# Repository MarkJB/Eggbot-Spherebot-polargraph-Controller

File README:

CCNC 2015 Copyright Mark Benson etc etc

This is my Arduino Nano/Stepstick Eggbot/Shperebot/Polargraph control board.

This has been used sucessfully with a 3d printed Eggbot and Polargraph. Firmwares adapted for this board available in github.com/markjb.

Designed in Kicad and custom kicad libs included.

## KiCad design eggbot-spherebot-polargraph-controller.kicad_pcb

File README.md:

CC BY-NC-SA 2016 Copyright Mark Benson etc etc

__Note: The v2.1 board is missing a power track between U2 & U3. You will need to solder a jumper wire between the Vin pins or Stepper1 (U2) will not move!__ (This has been fixed with v2.2)

This is my Arduino Nano - Dual Stepstick drawing machine controller PCB for Eggbot/Shperebot/polargraph drawing machines. The reason this uses an Arduino Nano and external stepstick drivers is that they can be found on ebay for not much money and I wanted this to be an affordable way to build the electronics for various drawing machines.

This has been used sucessfully with a 3d printed Eggbot and polargraph. Firmwares adapted for this board available in github.com/markjb. I've also seen it working with the Gocupi firmware.

Micro-stepping is software controlled and both steppers share the same 3 Arduino pins, so you only need configure those 3 pins to set the micro stepping for both steppers.

Assembly should be straight forward.

Orientation of U1, U2 & U3 can be determined by matching the pin names.

Orientation of C1 & C2 is negative to white half of silkscreen.

P1 & P2 (Stepper motors) are wired (from pin 1) A1, A2, B1, B2

P3 & P4 (End stops) are wired for 'Makerbot' style end stops and are wired (from pin 1) Vcc, Gnd, Gnd, Signal

P5 (Servo) is wired (from pin 1) Signal, Vcc, Gnd

BoM

| QTY | Description |
| --- | ---|
| 1 | PCB |
| 1 | Arduino Nano (U1) |
| 2 | Stepstick stepper motor driver boards (DRV8825 or A4988) (U2,U3) |
| 2 | 100uF 35v Electrolitic Capacitor (C1, C2) |
| 4 | 8 way female header (U2,U3) |
| 2 | 15 way female header (these are hard to come by, but 16 way headers are much easier to find and will work if you cut off one of the end pins) (U1) |
| 1 | 6 way female header (P7) |
| 4 | 4 way male header (P1,P2,P3,P4) |
| 1 | 3 way male header (P5) |
| 1 | 2 way male header (P6) |
| 1 | 2 way jumper (P6) |
| 1 | DC socket (CON1) |

EXT PWR = External Power. Enables or disables powering the Arduino from the DC supply. I've had a few Arduino Nano clones go up in smoke when used with both external and USB power. Leave the jumper off EXT PWR unless you have a really good reason for wanting to power the Arduino from the DC supply. I had hoped to be able to enable the SPI SD card and load the command queue onto that and run long Polargrapgh drawings from that on DC power alone, but there are issues with firmware size.

End stops are optional. Might be useful on an Eggbot/Spherebot.

Designed in Kicad 4.0.x. Custom kicad libs included.

PCBs manufactured by iTead Studios PCB prototyping service https://www.itead.cc/open-pcb/pcb-prototyping.html

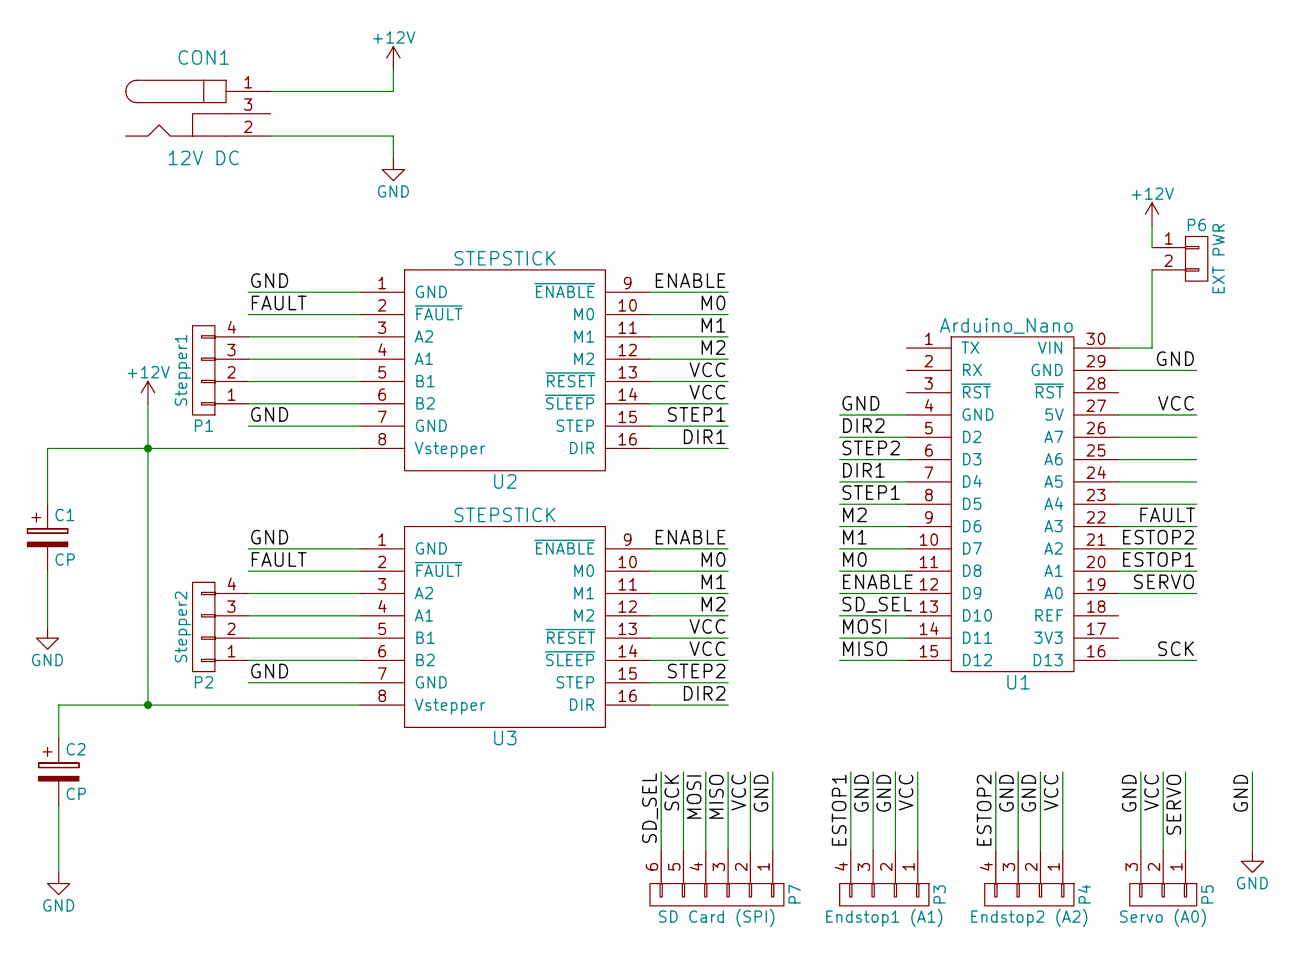
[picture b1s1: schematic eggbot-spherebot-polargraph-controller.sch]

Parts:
C1, C2: CP; C_Radial_D6.3_L11.2_P2.5
CON1: 12V DC; BARREL_JACK
P1: Stepper1; Pin_Header_Straight_1x04
P2: Stepper2; Pin_Header_Straight_1x04
P3: Endstop1 (A1); Pin_Header_Straight_1x04
P4: Endstop2 (A2); Pin_Header_Straight_1x04
P5: Servo (A0); Pin_Header_Straight_1x03
P6: EXT PWR; Pin_Header_Straight_1x02
P7: SD Card (SPI); Pin_Header_Straight_1x06
U1: Arduino_Nano; Arduino_nano_v3
U2, U3: STEPSTICK; Stepstick

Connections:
+12V: C1.1, C2.1, CON1.1, P6.1, U2.8 (Vstepper), U3.8 (Vstepper)
/DIR1: U1.7 (D4), U2.16 (DIR)
/DIR2: U1.5 (D2), U3.16 (DIR)
/ENABLE: U1.12 (D9), U2.9 (~ENABLE), U3.9 (~ENABLE)
/ESTOP1: P3.4, U1.20 (A1)
/ESTOP2: P4.4, U1.21 (A2)
/FAULT: U1.22 (A3), U2.2 (~FAULT), U3.2 (~FAULT)
/M0: U1.11 (D8), U2.10 (M0), U3.10 (M0)
/M1: U1.10 (D7), U2.11 (M1), U3.11 (M1)
/M2: U1.9 (D6), U2.12 (M2), U3.12 (M2)
/MISO: P7.3, U1.15 (D12)
/MOSI: P7.4, U1.14 (D11)
/SCK: P7.5, U1.16 (D13)
/SD_SEL: P7.6, U1.13 (D10)
/SERVO: P5.1, U1.19 (A0)
/STEP1: U1.8 (D5), U2.15 (STEP)
/STEP2: U1.6 (D3), U3.15 (STEP)
/VCC: P3.1, P4.1, P5.2, P7.2, U1.27 (5V), U2.13 (~RESET), U2.14 (~SLEEP), U3.13 (~RESET), U3.14 (~SLEEP)
GND: C1.2, C2.2, CON1.2, P3.2, P3.3, P4.2, P4.3, P5.3, P7.1, U1.4 (GND), U1.29 (GND), U2.1 (GND), U2.7 (GND), U3.1 (GND), U3.7 (GND)
unnamed: P1.1, U2.6 (B2)
unnamed: P1.2, U2.5 (B1)
unnamed: P1.3, U2.4 (A1)
unnamed: P1.4, U2.3 (A2)
unnamed: P2.1, U3.6 (B2)
unnamed: P2.2, U3.5 (B1)
unnamed: P2.3, U3.4 (A1)
unnamed: P2.4, U3.3 (A2)
unnamed: P6.2, U1.30 (VIN)

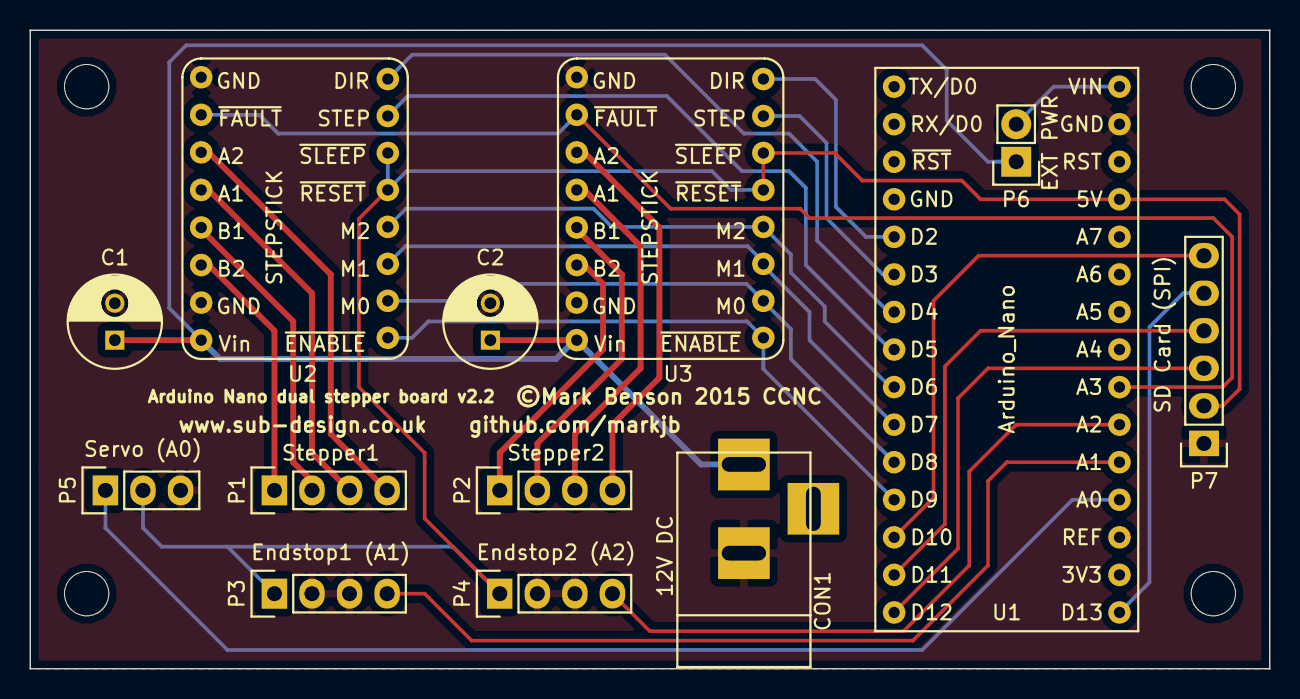
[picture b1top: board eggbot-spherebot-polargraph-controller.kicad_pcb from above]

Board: 2 copper layers, 83.8 x 43.2 mm, 13 parts (0 on the bottom side), 28 nets.

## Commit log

2015-11-04 :neckbeard: Added .gitattributes & .gitignore files
2015-11-04 Added image to readme
2015-11-04 Rename README to README.md
2016-03-05 Renamed kicad project - added pdf of schematic
2016-03-05 Added schematic png
2016-03-05 Updated 3D renders of PCB
2016-03-06 Updated readme and licence details

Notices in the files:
eggbot-spherebot-polargraph-controller.kicad_pcb:
©Mark Benson 2015 CCNC
